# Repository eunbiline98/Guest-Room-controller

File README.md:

# Guest-Room-controller
dev Load Controller Guest-Room-controller Mqtt protocol home assistant support

# Guest-Room-controller V.1
- SoC board esp32
- 6 Or 8 Group Relay Omron M2YN
- Support Led Stip adressing WS2812/WS2811
- Home Assistant Integrated Or Stand Alone
# 8 Zone 
# 6 Zone 

# Guest-Room-controller V.2
- SoC board esp32
- 5 Group Relay SPDT 
- 3 Group Dimmer 0-10V
-  Stand Alone ( Next Home Assistant Integrated )
# 

# Smart Switch Momentary
https://github.com/eunbiline98/Smart-Switch-Momentary-

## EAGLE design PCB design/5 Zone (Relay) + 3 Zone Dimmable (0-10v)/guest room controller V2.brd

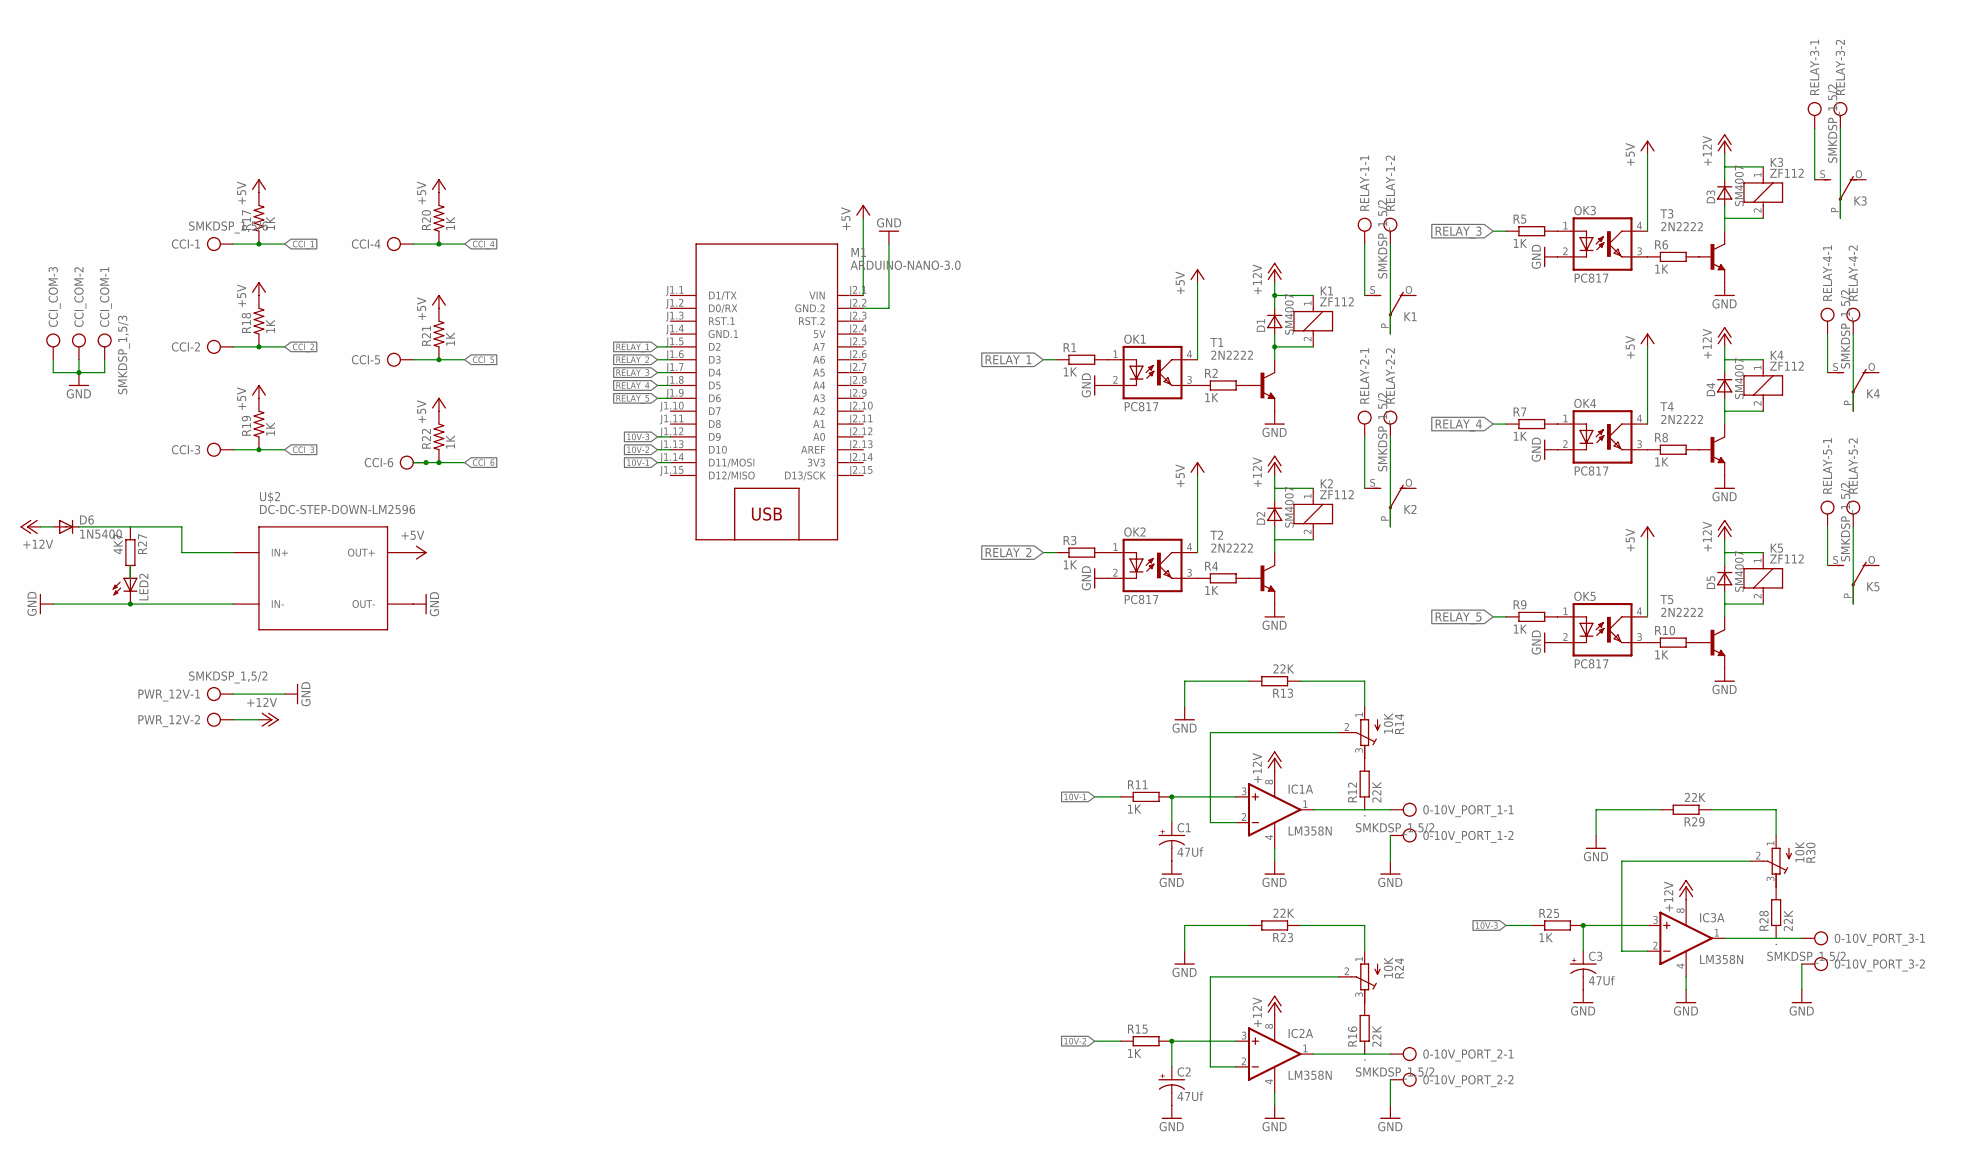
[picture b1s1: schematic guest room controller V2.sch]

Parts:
0-10V_PORT_1, 0-10V_PORT_2, 0-10V_PORT_3: SMKDSP_1,5/2
C1, C2, C3: 47Uf; E2,5-6
CCI: SMKDSP_1,5/6
CCI_COM: SMKDSP_1,5/3
D1, D2, D3, D4, D5: SM4007; MELF-MLL41
D6: 1N5400; DO201-15
IC1, IC2, IC3: LM358N; DIL08
K1, K2, K3, K4, K5: ZF112
LED2: LED3MM
M1: ARDUINO-NANO-3.0
OK1, OK2, OK3, OK4, OK5: PC817; DIL04
PWR_12V: SMKDSP_1,5/2
R1, R2, R3, R4, R5, R6, R7, R8, R9, R10, R11, R15, R25: 1K; 0207/10
R12, R13, R16, R23, R28, R29: 22K; 0207/10
R14, R24, R30: 10K; RTRIM64P
R17, R18, R19, R20, R21, R22: 1K; R1206
R27: 4K7; 0207/10
RELAY-1, RELAY-2, RELAY-3, RELAY-4, RELAY-5: SMKDSP_1,5/2
T1, T2, T3, T4, T5: 2N2222; TO18
U$2: DC-DC-STEP-DOWN-LM2596

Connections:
3V3: M1.J2.14 (3V3)
5V: M1.J2.4 (5V)
10V-1: M1.J1.14 (D11/MOSI), R11.1
10V-2: M1.J1.13 (D10), R15.1
10V-3: M1.J1.12 (D9), R25.1
+5V: M1.J2.1 (VIN), OK1.4 (COL), OK2.4 (COL), OK3.4 (COL), OK4.4 (COL), OK5.4 (COL), R17.2, R18.2, R19.2, R20.2, R21.2, R22.2, U$2.OUT+
+12V: D1.C, D2.C, D3.C, D4.C, D5.C, D6.A, IC1.8 (V+), IC2.8 (V+), IC3.8 (V+), K1.1, K2.1, K3.1, K4.1, K5.1, PWR_12V.2
CCI_1: CCI.1, R17.1
CCI_2: CCI.2, R18.1
CCI_3: CCI.3, R19.1
CCI_4: CCI.4, R20.1
CCI_5: CCI.5, R21.1
CCI_6: CCI.6, R22.1
GND: 0-10V_PORT_1.2, 0-10V_PORT_2.2, 0-10V_PORT_3.2, C1.-, C2.-, C3.-, CCI_COM.1, CCI_COM.2, CCI_COM.3, IC1.4 (V-), IC2.4 (V-), IC3.4 (V-), LED2.K (C), M1.J2.2 (GND.2), OK1.2 (C), OK2.2 (C), OK3.2 (C), OK4.2 (C), OK5.2 (C), PWR_12V.1, R13.2, R23.2, R29.2, T1.1 (E), T2.1 (E), T3.1 (E), T4.1 (E), T5.1 (E), U$2.IN-, U$2.OUT-
GND.1: M1.J1.4 (GND.1)
unnamed: OK1.3 (EMIT), R2.1
unnamed: R2.2, T1.2 (B)
unnamed: D1.A, K1.2, T1.3 (C)
unnamed: OK2.3 (EMIT), R4.1
unnamed: R4.2, T2.2 (B)
unnamed: D2.A, K2.2, T2.3 (C)
unnamed: OK3.3 (EMIT), R6.1
unnamed: R6.2, T3.2 (B)
unnamed: D3.A, K3.2, T3.3 (C)
unnamed: OK4.3 (EMIT), R8.1
unnamed: R8.2, T4.2 (B)
unnamed: D4.A, K4.2, T4.3 (C)
unnamed: OK5.3 (EMIT), R10.1
unnamed: R10.2, T5.2 (B)
unnamed: D5.A, K5.2, T5.3 (C)
unnamed: K1.S, RELAY-1.1
unnamed: LED2.A, R27.2
unnamed: C1.+, IC1.3 (+IN), R11.2
unnamed: 0-10V_PORT_1.1, IC1.1 (OUT), R12.1
unnamed: R12.2, R14.3 (E)
unnamed: IC1.2 (-IN), R14.2 (S)
unnamed: R13.1, R14.1 (A)
unnamed: C2.+, IC2.3 (+IN), R15.2
unnamed: OK1.1 (A), R1.2
unnamed: OK2.1 (A), R3.2
unnamed: OK3.1 (A), R5.2
unnamed: OK4.1 (A), R7.2
unnamed: OK5.1 (A), R9.2
unnamed: 0-10V_PORT_2.1, IC2.1 (OUT), R16.1
unnamed: D6.C, R27.1, U$2.IN+
unnamed: K1.P, RELAY-1.2
unnamed: R16.2, R24.3 (E)
unnamed: K2.S, RELAY-2.1
unnamed: IC2.2 (-IN), R24.2 (S)
unnamed: R23.1, R24.1 (A)
unnamed: C3.+, IC3.3 (+IN), R25.2
unnamed: 0-10V_PORT_3.1, IC3.1 (OUT), R28.1
unnamed: R28.2, R30.3 (E)
unnamed: IC3.2 (-IN), R30.2 (S)
unnamed: R29.1, R30.1 (A)
unnamed: K2.P, RELAY-2.2
unnamed: K3.S, RELAY-3.1
unnamed: K3.P, RELAY-3.2
unnamed: K4.P, RELAY-4.2
unnamed: K4.S, RELAY-4.1
unnamed: K5.P, RELAY-5.2
unnamed: K5.S, RELAY-5.1
RELAY_1: M1.J1.5 (D2), R1.1
RELAY_2: M1.J1.6 (D3), R3.1
RELAY_3: M1.J1.7 (D4), R5.1
RELAY_4: M1.J1.8 (D5), R7.1
RELAY_5: M1.J1.9 (D6), R9.1

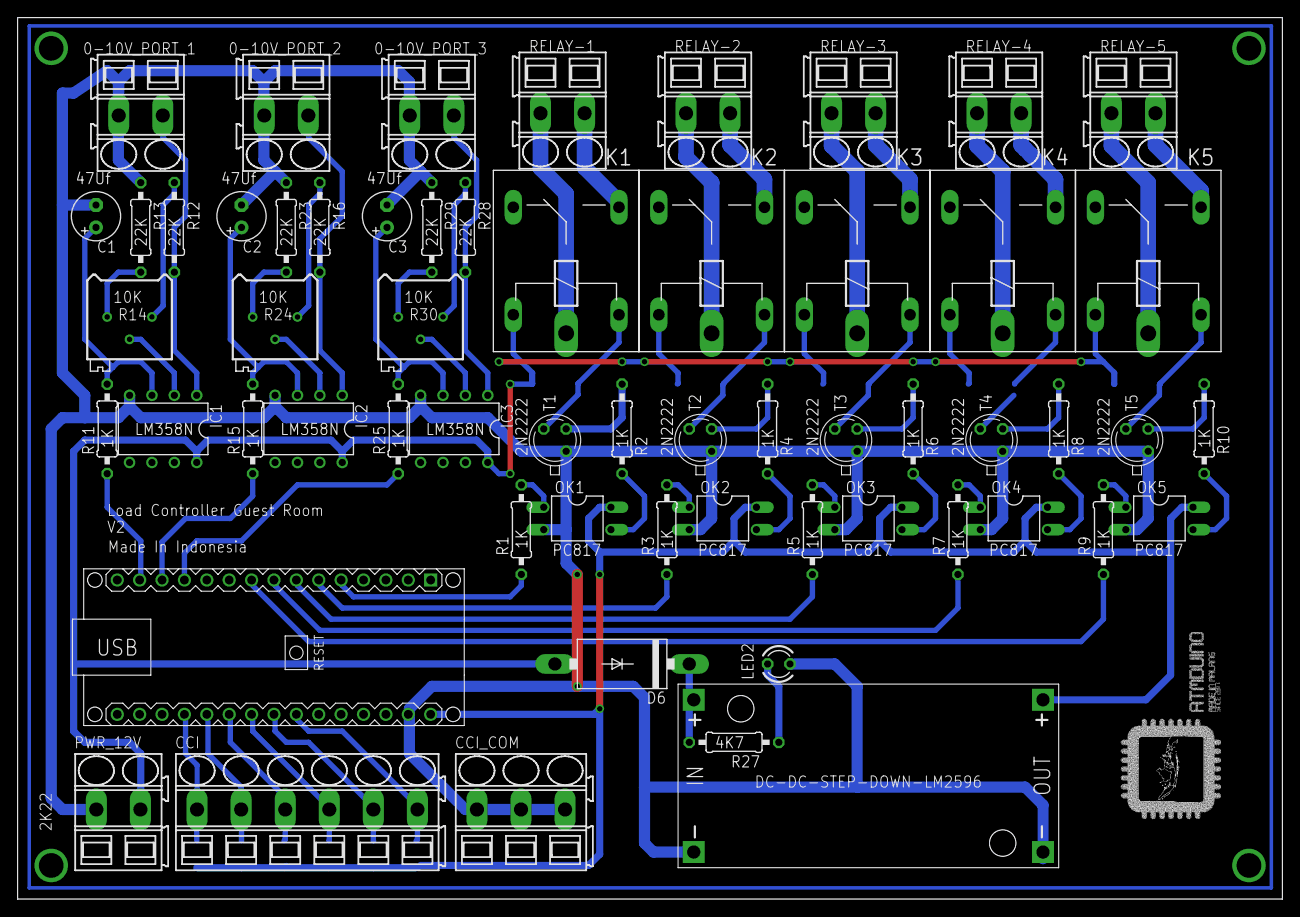
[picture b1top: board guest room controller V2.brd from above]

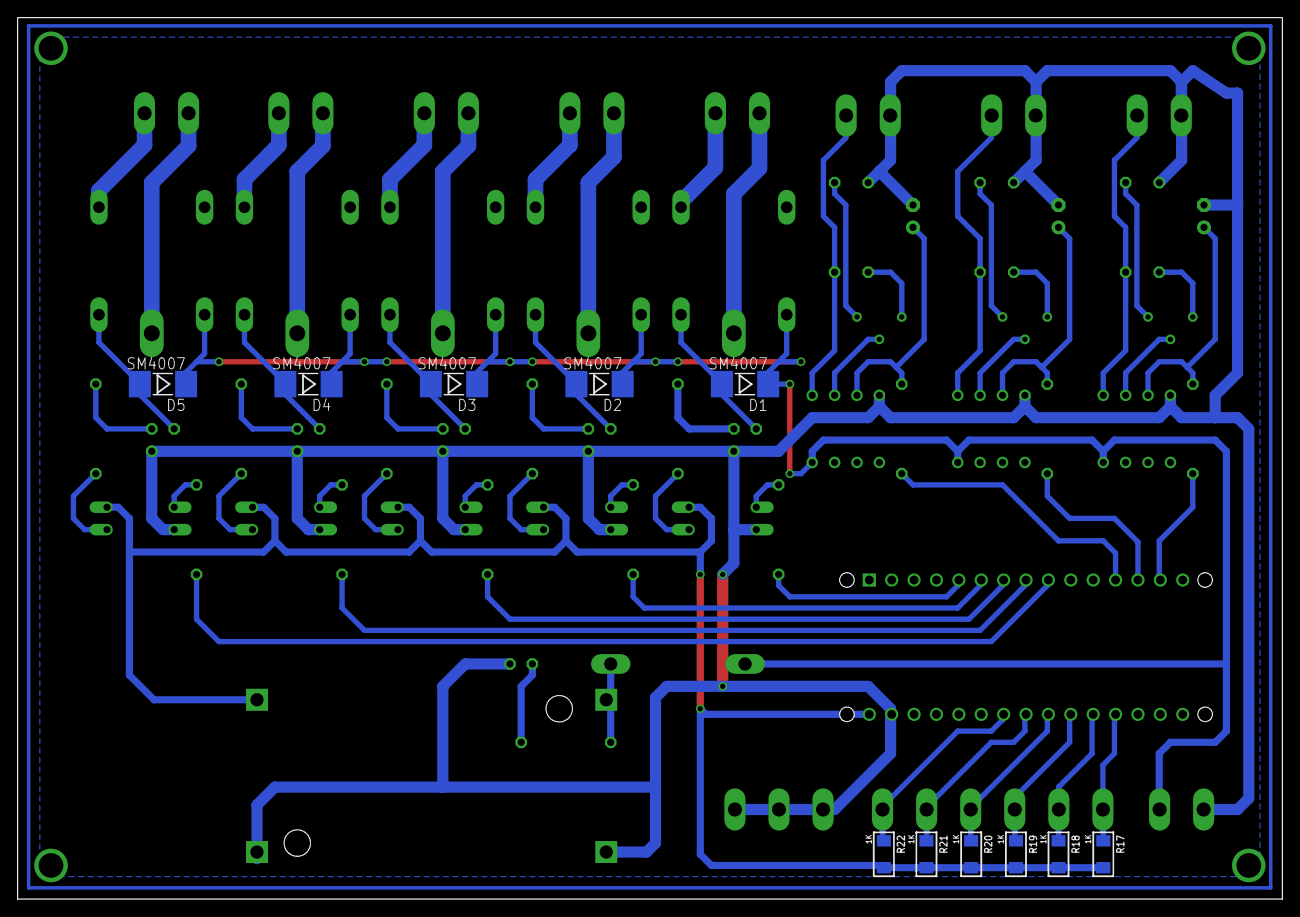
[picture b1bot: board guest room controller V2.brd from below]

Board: 2 copper layers, 143.5 x 100.0 mm, 70 parts (11 on the bottom side), 64 nets.

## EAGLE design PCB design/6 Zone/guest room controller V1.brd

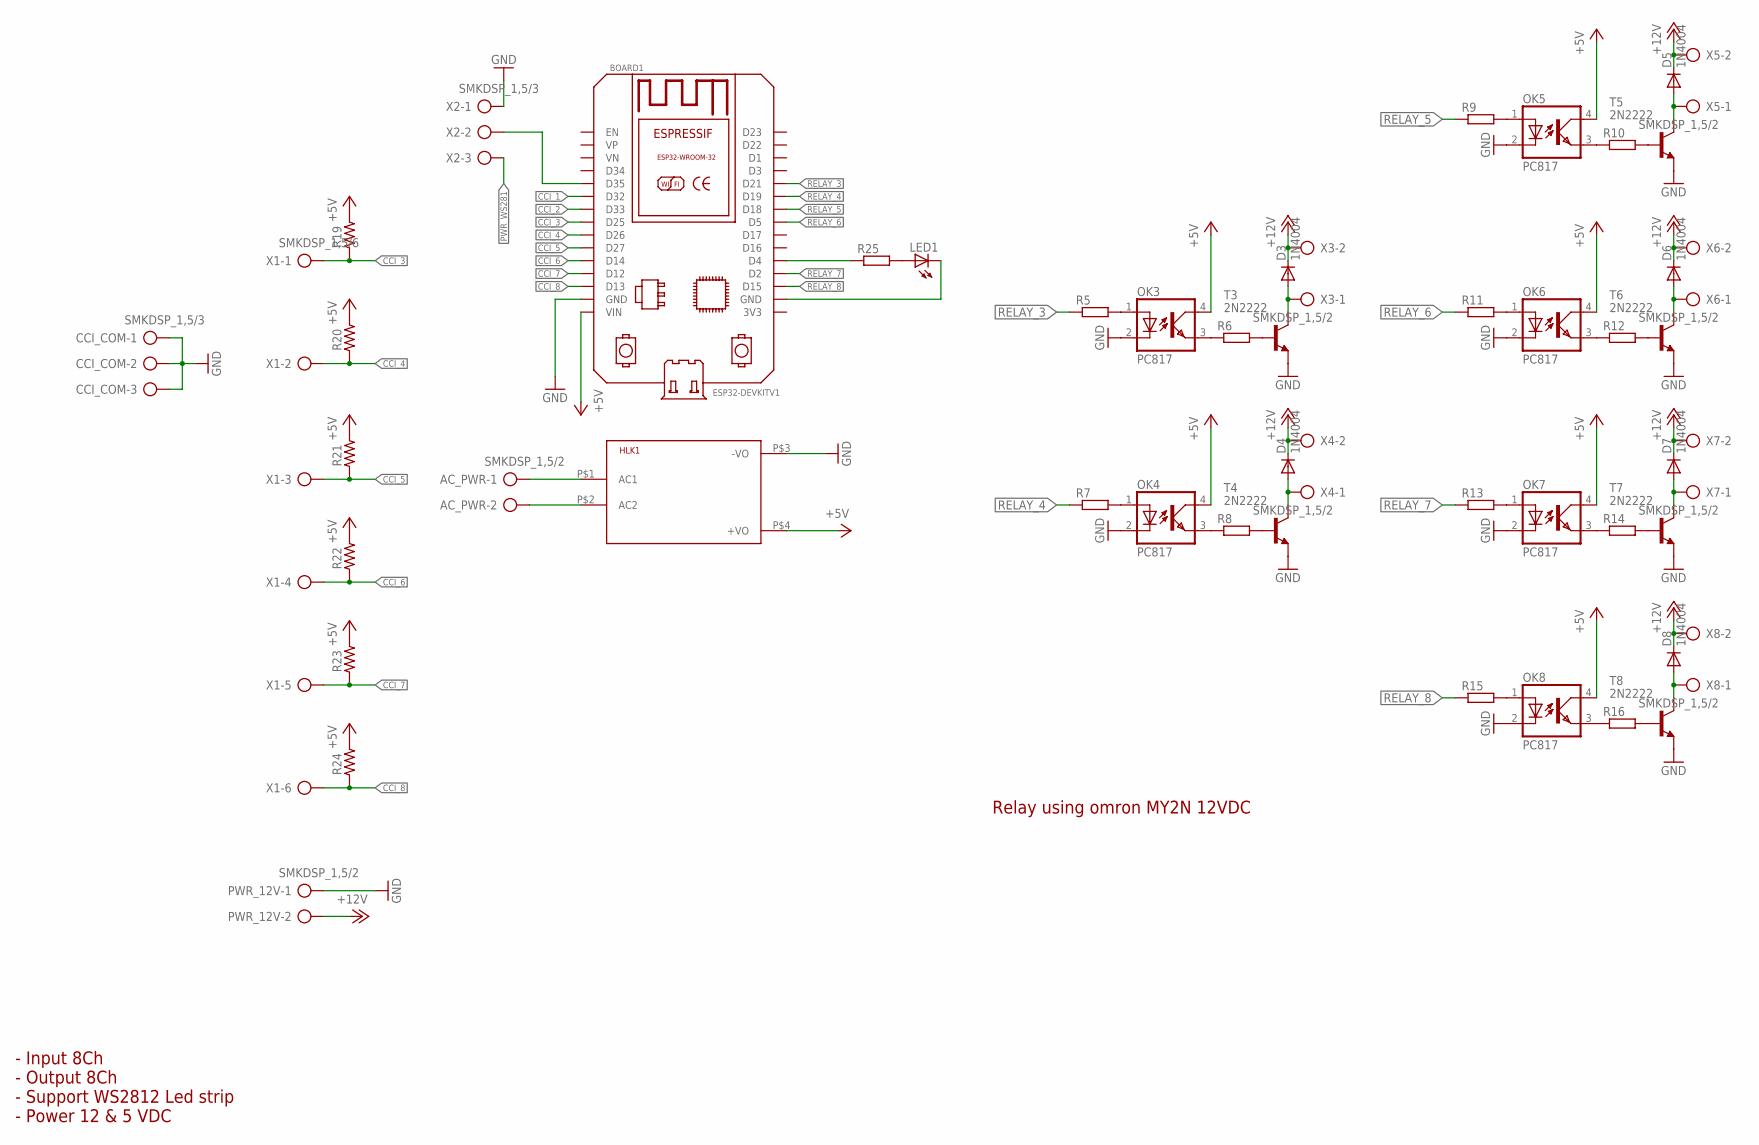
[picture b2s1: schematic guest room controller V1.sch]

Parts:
AC_PWR: SMKDSP_1,5/2
BOARD1: ESP32DEVKITV1; ESP32-DEVKITV1
CCI_COM: SMKDSP_1,5/3
D3, D4, D5, D6, D7, D8: 1N4004; DO41-10
HLK1: HLK-PM013W; HLK-PM01
LED1: LED3MM
OK3, OK4, OK5, OK6, OK7, OK8: PC817; DIL04
PWR_12V: SMKDSP_1,5/2
R5, R6, R7, R8, R9, R10, R11, R12, R13, R14, R15, R16, R25: R-EU_0207/10; 0207/10
R19, R20, R21, R22, R23, R24: R_1206; R1206
T3, T4, T5, T6, T7, T8: 2N2222; TO18
X1: SMKDSP_1,5/6
X2: SMKDSP_1,5/3
X3, X4, X5, X6, X7, X8: SMKDSP_1,5/2

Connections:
+5V: BOARD1.VIN, HLK1.P$4 (+VO), OK3.4 (COL), OK4.4 (COL), OK5.4 (COL), OK6.4 (COL), OK7.4 (COL), OK8.4 (COL), R19.2, R20.2, R21.2, R22.2, R23.2, R24.2
+12V: D3.C, D4.C, D5.C, D6.C, D7.C, D8.C, PWR_12V.2, X3.2, X4.2, X5.2, X6.2, X7.2, X8.2
CCI_1: BOARD1.D32
CCI_2: BOARD1.D33
CCI_3: BOARD1.D25, R19.1, X1.1
CCI_4: BOARD1.D26, R20.1, X1.2
CCI_5: BOARD1.D27, R21.1, X1.3
CCI_6: BOARD1.D14, R22.1, X1.4
CCI_7: BOARD1.D12, R23.1, X1.5
CCI_8: BOARD1.D13, R24.1, X1.6
GND: BOARD1.GND, CCI_COM.1, CCI_COM.2, CCI_COM.3, HLK1.P$3 (-VO), OK3.2 (C), OK4.2 (C), OK5.2 (C), OK6.2 (C), OK7.2 (C), OK8.2 (C), PWR_12V.1, T3.1 (E), T4.1 (E), T5.1 (E), T6.1 (E), T7.1 (E), T8.1 (E), X2.1
unnamed: OK3.3 (EMIT), R6.1
unnamed: R6.2, T3.2 (B)
unnamed: D3.A, T3.3 (C), X3.1
unnamed: OK4.3 (EMIT), R8.1
unnamed: R8.2, T4.2 (B)
unnamed: D4.A, T4.3 (C), X4.1
unnamed: OK5.3 (EMIT), R10.1
unnamed: R10.2, T5.2 (B)
unnamed: D5.A, T5.3 (C), X5.1
unnamed: OK6.3 (EMIT), R12.1
unnamed: R12.2, T6.2 (B)
unnamed: D6.A, T6.3 (C), X6.1
unnamed: OK7.3 (EMIT), R14.1
unnamed: R14.2, T7.2 (B)
unnamed: D7.A, T7.3 (C), X7.1
unnamed: OK8.3 (EMIT), R16.1
unnamed: R16.2, T8.2 (B)
unnamed: D8.A, T8.3 (C), X8.1
unnamed: AC_PWR.1, HLK1.P$1 (AC1)
unnamed: OK3.1 (A), R5.2
unnamed: OK4.1 (A), R7.2
unnamed: OK5.1 (A), R9.2
unnamed: OK6.1 (A), R11.2
unnamed: OK7.1 (A), R13.2
unnamed: OK8.1 (A), R15.2
unnamed: BOARD1.D4, R25.1
unnamed: LED1.A, R25.2
unnamed: BOARD1.GND@1 (GND), LED1.K (C)
unnamed: BOARD1.D35, X2.2
unnamed: AC_PWR.2, HLK1.P$2 (AC2)
PWR_WS281: X2.3
RELAY_3: BOARD1.D21, R5.1
RELAY_4: BOARD1.D19, R7.1
RELAY_5: BOARD1.D18, R9.1
RELAY_6: BOARD1.D5, R11.1
RELAY_7: BOARD1.D2, R13.1
RELAY_8: BOARD1.D15, R15.1

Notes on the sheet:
- Input 8Ch - Output 8Ch - Support WS2812 Led strip - Power 12 & 5 VDC
Relay using omron MY2N 12VDC

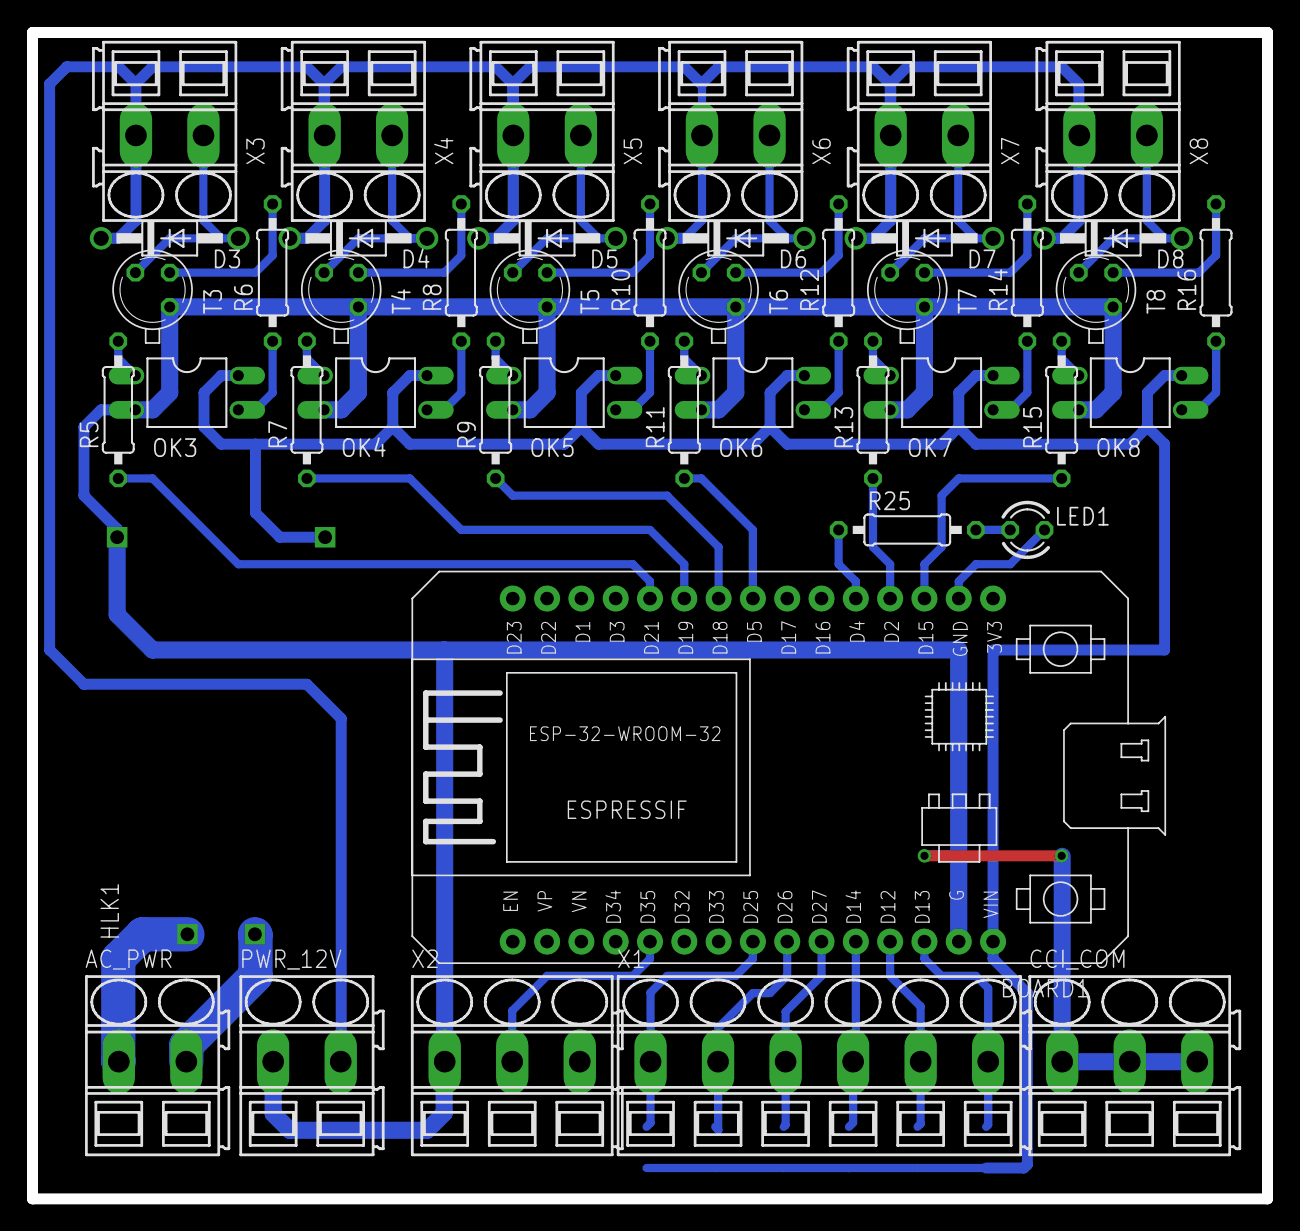
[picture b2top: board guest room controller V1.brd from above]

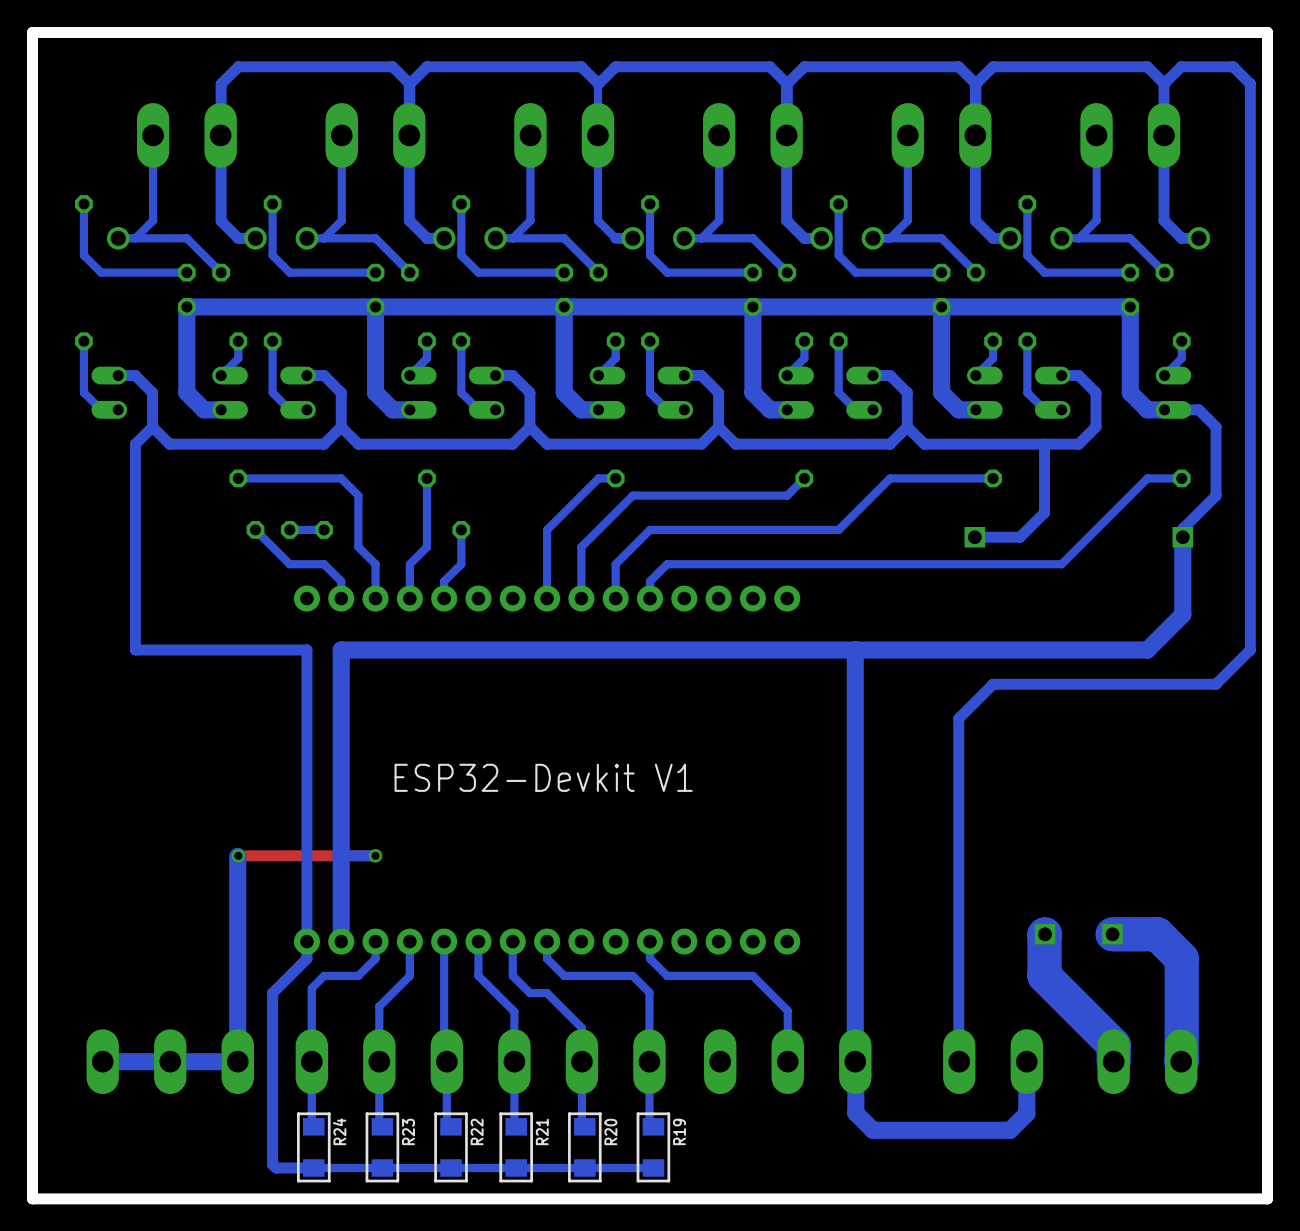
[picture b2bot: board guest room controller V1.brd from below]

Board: 2 copper layers, 91.4 x 86.4 mm, 51 parts (6 on the bottom side), 45 nets.

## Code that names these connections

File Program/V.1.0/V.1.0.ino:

#include <WiFi.h>
#include <PubSubClient.h>

const char *ssid = "Kost Pak Josa";
const char *password = "joputra1";
const char *MQTT_SERVER = "192.168.1.21";

const char *MQTT_TOPIC1 = "relay/1/state";
const char *MQTT_TOPIC2 = "relay/2/state";
const char *MQTT_TOPIC3 = "relay/3/state";
const char *MQTT_TOPIC4 = "relay/4/state";
const char *MQTT_TOPIC5 = "relay/5/state";
const char *MQTT_TOPIC6 = "relay/6/state";
const char *MQTT_TOPIC7 = "relay/7/state";
const char *MQTT_TOPIC8 = "relay/8/state";

const char *R1 = "relay/1/cmd";
const char *R2 = "relay/2/cmd";
const char *R3 = "relay/3/cmd";
const char *R4 = "relay/4/cmd";
const char *R5 = "relay/5/cmd";
const char *R6 = "relay/6/cmd";
const char *R7 = "relay/7/cmd";
const char *R8 = "relay/8/cmd";

const char *MQTT_CLIENT_ID = "guest_room_1";
const char *MQTT_USERNAME = "admin";
const char *MQTT_PASSWORD = "admin";

WiFiClient espClient;
PubSubClient client(espClient);

// Pin Setup
#define relay_1 15
#define relay_2 12
#define relay_3 5
#define relay_4 18
#define relay_5 19
#define relay_6 21
#define relay_7 22
#define relay_8 23

#define keyCard 13
#define btn_1 12
#define btn_2 14
#define btn_3 27
#define btn_4 26
#define btn_5 25

int lastMilis = 0;
unsigned long nowMillis = millis();

void setup_wifi()
{
  // Connect to Wifi Network
  pinMode(4, OUTPUT); // WiFi Indicator
  Serial.println();
  Serial.print("Connecting to ");
  Serial.println(ssid);

  WiFi.begin(ssid, password);

  while (WiFi.status() != WL_CONNECTED)
  {
    digitalWrite(4, HIGH);
    delay(80);
    digitalWrite(4, LOW);
    delay(80);
  }

  Serial.println("");
  Serial.println("WiFi connected");
  Serial.println("IP address: ");
  Serial.println(WiFi.localIP());
}

void callback(char *topic, byte *message, unsigned int length)
{
  Serial.print("Message arrived in topic: ");
  Serial.println(topic);
  Serial.print("Message:");
  String messageTemp;

  for (int i = 0; i < length; i++)
  {
    Serial.print((char)message[i]);
    Serial.println();
    if ((char)message[i] != '"')
      messageTemp += (char)message[i];
  }

  if (String(topic) == R1)
  {
    if (messageTemp == "1")
    {
      digitalWrite(relay_1, HIGH);
      client.publish(MQTT_TOPIC1, "1");
    }
    else if (messageTemp == "0")
    {
      digitalWrite(relay_1, LOW);
       client.publish(MQTT_TOPIC1,"0");
    }
  }

  if (String(topic) == R2)
  {
    if (messageTemp == "1")
    {
      digitalWrite(relay_2, HIGH);
      client.publish(MQTT_TOPIC2,"1");
    }
    else if (messageTemp == "0")
    {
      digitalWrite(relay_2, LOW);
      client.publish(MQTT_TOPIC2,"0");
    }
  }

  if (String(topic) == R3)
  {
    if (messageTemp == "1")
    {
      digitalWrite(relay_3, HIGH);
      client.publish(MQTT_TOPIC3,"1");
    }
    else if (messageTemp == "0")
    {
      digitalWrite(relay_3, LOW);
      client.publish(MQTT_TOPIC3,"0");
    }
  }

  if (String(topic) == R4)
  {
    if (messageTemp == "1")
    {
      digitalWrite(relay_4, HIGH);
      client.publish(MQTT_TOPIC4,"1");
    }
    else if (messageTemp == "0")
    {
      digitalWrite(relay_4, LOW);
      client.publish(MQTT_TOPIC4,"0");
    }
  }

  if (String(topic) == R5)
  {
    if (messageTemp == "1")
    {
      digitalWrite(relay_5, HIGH);
      client.publish(MQTT_TOPIC5,"1");
    }
    else if (messageTemp == "0")
    {
      digitalWrite(relay_5, LOW);
      client.publish(MQTT_TOPIC5,"0");
    }
  }

  if (String(topic) == R6)
  {
    if (messageTemp == "1")
    {
      digitalWrite(relay_6, HIGH);
      client.publish(MQTT_TOPIC6,"1");
    }
    else if (messageTemp == "0")
    {
      digitalWrite(relay_6, LOW);
      client.publish(MQTT_TOPIC6,"0");
    }
  }

  if (String(topic) == R7)
  {
    if (messageTemp == "1")
    {
      digitalWrite(relay_7, HIGH);
      client.publish(MQTT_TOPIC7,"1");
    }
    else if (messageTemp == "0")
    {
      digitalWrite(relay_7, LOW);
      client.publish(MQTT_TOPIC7,"0");
    }
  }

  if (String(topic) == R8)
  {
    if (messageTemp == "1")
    {
      digitalWrite(relay_8, HIGH);
      client.publish(MQTT_TOPIC8,"1");
    }
    else if (messageTemp == "0")
    {
      digitalWrite(relay_8, LOW);
      client.publish(MQTT_TOPIC8,"0");
    }
  }
}

void reconnect()
{
  // Loop until we're reconnected
  while (!client.connected())
  {
    Serial.print("Attempting MQTT connection...");
    // Attempt to connect
    if (client.connect(MQTT_CLIENT_ID, MQTT_USERNAME, MQTT_PASSWORD))
    {
      Serial.println("connected");
      // subscribe
      client.subscribe(R1);
      client.subscribe(R2);
      client.subscribe(R3);
      client.subscribe(R4);
      client.subscribe(R5);
      client.subscribe(R6);
      client.subscribe(R7);
      client.subscribe(R8);
    }
    else
    {
      Serial.print("failed, rc=");
      Serial.print(client.state());
      Serial.println(" try again in 5 seconds");
      // Wait 5 seconds before retrying
      delay(5000);
    }
  }
}

void setup()
{
  // Serial port for debugging purposes
  Serial.begin(115200);
  setup_wifi();

  // MQTT Server Setup
  client.setServer(MQTT_SERVER, 1883);
  client.setCallback(callback);

  pinMode(4, OUTPUT); // WiFi Indicator
  pinMode(relay_1, OUTPUT);
  pinMode(relay_2, OUTPUT);
  pinMode(relay_3, OUTPUT);
  pinMode(relay_4, OUTPUT);
  pinMode(relay_5, OUTPUT);
  pinMode(relay_6, OUTPUT);
  pinMode(relay_7, OUTPUT);
  pinMode(relay_8, OUTPUT);

  pinMode(btn_1, INPUT);
  pinMode(btn_2, INPUT);
  pinMode(btn_3, INPUT);
  pinMode(btn_4, INPUT);
  pinMode(btn_5, INPUT);
  pinMode(keyCard, INPUT);
}

void loop()
{
  if (!client.connected())
  {
    reconnect();
  }
  client.loop();
}

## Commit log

2022-01-31 adding PCB design V.1
2022-02-10 Adding Program Test Hadware
2022-02-10 Adding Program Test Module 0-10V
2022-02-10 Adding PCB Design
2022-02-10 Adding File Gerber

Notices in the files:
parts and their libraries:
rc-master-smd: Copyright (C) 2007, Bob Starr
diy-modules: Released under the Creative Commons Attribution 4.0 International License: http://creativecommons.org/licenses/by/4.0
